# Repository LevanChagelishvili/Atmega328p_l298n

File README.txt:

Atmega328p L298N motor driver, KiCad PCB and Proteus simulation

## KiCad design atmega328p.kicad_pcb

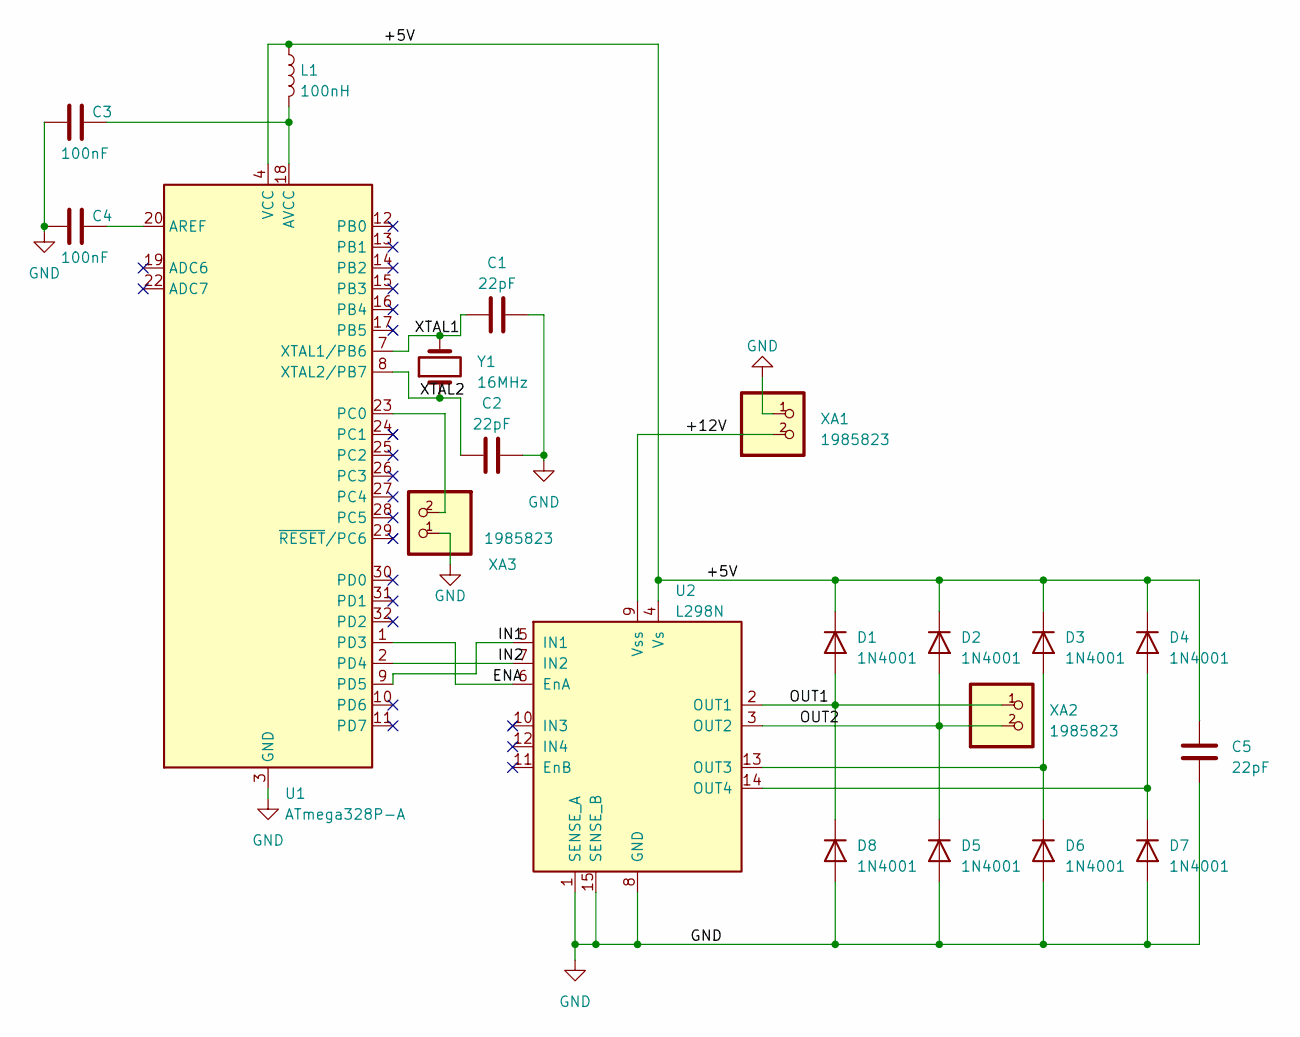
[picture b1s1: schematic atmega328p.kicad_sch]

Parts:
C1, C2, C5: 22pF; C_0201_0603Metric_Pad0.64x0.40mm_HandSolder
C3, C4: 100nF; C_0402_1005Metric_Pad0.74x0.62mm_HandSolder
D1, D2, D3, D4, D5, D6, D7, D8: 1N4001; D_DO-41_SOD81_P10.16mm_Horizontal
L1: 100nH; L_7.3x7.3_H4.5
U1: ATmega328P-A; TQFP-32_7x7mm_P0.8mm
U2: L298N; TO-220-15_P2.54x2.54mm_StaggerOdd_Lead4.58mm_Vertical
XA1, XA2, XA3: 1985823; TerminalBlock_Phoenix_MKDS-1,5-2-5.08_1x02_P5.08mm_Horizont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
Y1: 16MHz; Crystal_HC18-U_Vertical

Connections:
/+5V: C5.2, D1.1 (K), D2.1 (K), D3.1 (K), D4.1 (K), L1.1, U1.4 (VCC), U1.6 (VCC), U2.4 (Vs)
/+12V: U2.9 (Vss), XA1.2
/ENA: U1.1 (PD3), U2.6 (EnA)
/IN1: U1.9 (PD5), U2.5 (IN1)
/IN2: U1.2 (PD4), U2.7 (IN2)
/OUT1: D1.2 (A), D8.1 (K), U2.2 (OUT1), XA2.1
/OUT2: D2.2 (A), D5.1 (K), U2.3 (OUT2), XA2.2
/XTAL1: C1.1, U1.7 (XTAL1/PB6), Y1.2
/XTAL2: C2.1, U1.8 (XTAL2/PB7), Y1.1
GND: C1.2, C2.2, C3.2, C4.2, C5.1, D5.2 (A), D6.2 (A), D7.2 (A), D8.2 (A), U1.3 (GND), U1.5 (GND), U1.21 (GND), U2.1 (SENSE_A), U2.8 (GND), U2.15 (SENSE_B), XA1.1, XA3.1
unnamed: D3.2 (A), D6.1 (K), U2.13 (OUT3)
unnamed: D4.2 (A), D7.1 (K), U2.14 (OUT4)
unnamed: C4.1, U1.20 (AREF)
unnamed: C3.1, L1.2, U1.18 (AVCC)
unnamed: U1.23 (PC0), XA3.2

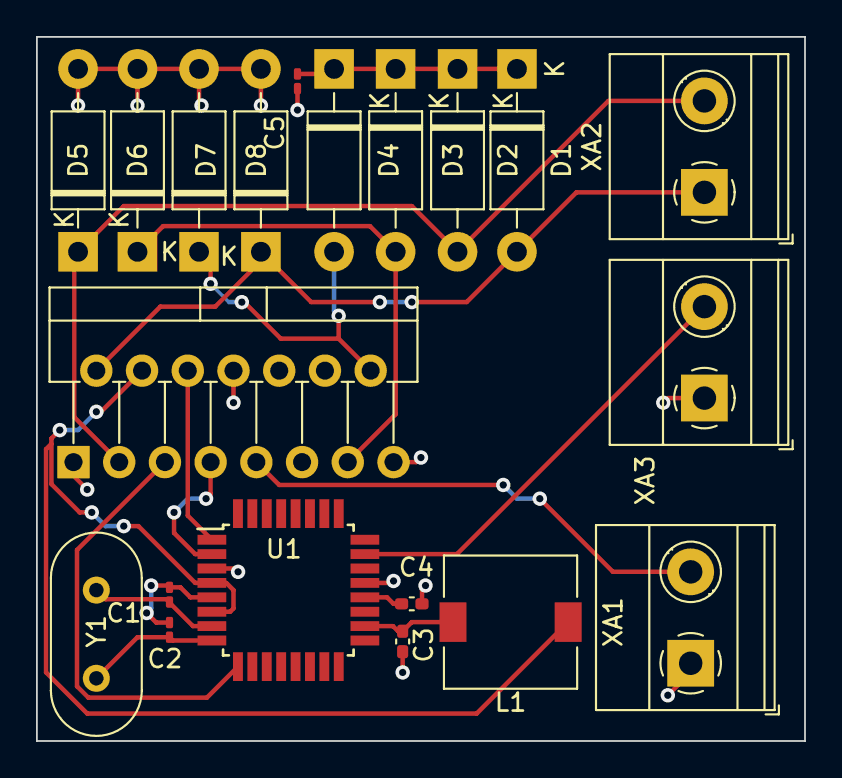
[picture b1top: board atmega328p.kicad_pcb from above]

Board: 2 copper layers, 42.7 x 39.1 mm, 20 parts (0 on the bottom side), 15 nets.
